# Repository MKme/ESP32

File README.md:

<p align="center">

<br>
🐦 <a href="https://twitter.com/mkmeorg">Twitter</a>
| 📺 <a href="https://www.youtube.com/mkmeorg">YouTube</a>
| 🌍 <a href="http://www.mkme.org">mkme.org</a><br>
Support this project and become a patron on <a href="http://mkme.org/patreon">Eric's Patreon</a>.<br>
Website, Forum and store are at http://mkme.org <br>
Chat with Me: <a href="https://discord.gg/j9S4Fgv">Discord</a></b>
</p>

Eric's ESP32 stuff for the various ESP32 boards and programming files in my collection.  Since the ESP32 is supported by MicroPython 
I will try to incorporate it in to more projects and videos as best I can.  

Buy an ESP32 Cam board here: https://amzn.to/2MMk2QP

Buy the ESP32 Lite Board here: https://amzn.to/2YDs3tN

Buy the OLED version here: https://amzn.to/36DUf4b

# Wemos ESP32 Lite Board

Buy the ESP 32 Lite on Amazon here: https://amzn.to/3coe2be

## Install Micropython

1.  Got to micropythong.org
2.  Download ESP32 Firmware for board
3.  Open Thonny and pick ESP32 on USB and flash firmware .bin
4.  Thonny Repl should be working  

## Wemos 32 Lite Reference Info Links

4MB Flash

Lithium battery interface, 500mA Max charging current

Default firmware: Lastest MicroPython firmware

Max serial baud rate: 256000bps

-  GPIO 22 has built in LED 

- No power LED so no wasted consumption

- https://diyprojects.io/wemos-lolin32-lite-compact-revision-lolin32-4-90/

- https://randomnerdtutorials.com/getting-started-micropython-esp32-esp8266/#:~:text=The%20code%20for%20blinking%20an%20LED%20on%20a,without%20the%20need%20to%20compile%20or%20upload%20code.

-  https://randomnerdtutorials.com/getting-started-micropython-esp32-esp8266/#:~:text=The%20code%20for%20blinking%20an%20LED%20on%20a,without%20the%20need%20to%20compile%20or%20upload%20code.

-  Not lite but same programming https://www.youtube.com/watch?v=BzAo48cFhS8&ab_channel=

# ESP 32 Cam Board

- See ResQ repo for updated ESP32 camera code but copied here for quick use

- Interesting Google Cam use https://www.youtube.com/watch?v=Upcr_rXnMQY&ab_channel=anyboards

- BME 280 I2C with ESP cam:  https://3iinc.xyz/blog/how-to-use-i2c-sensor-bme280-with-esp32cam/  

## FTDI Connections for programming: 
<br>

##  Arduino Settings for programming:

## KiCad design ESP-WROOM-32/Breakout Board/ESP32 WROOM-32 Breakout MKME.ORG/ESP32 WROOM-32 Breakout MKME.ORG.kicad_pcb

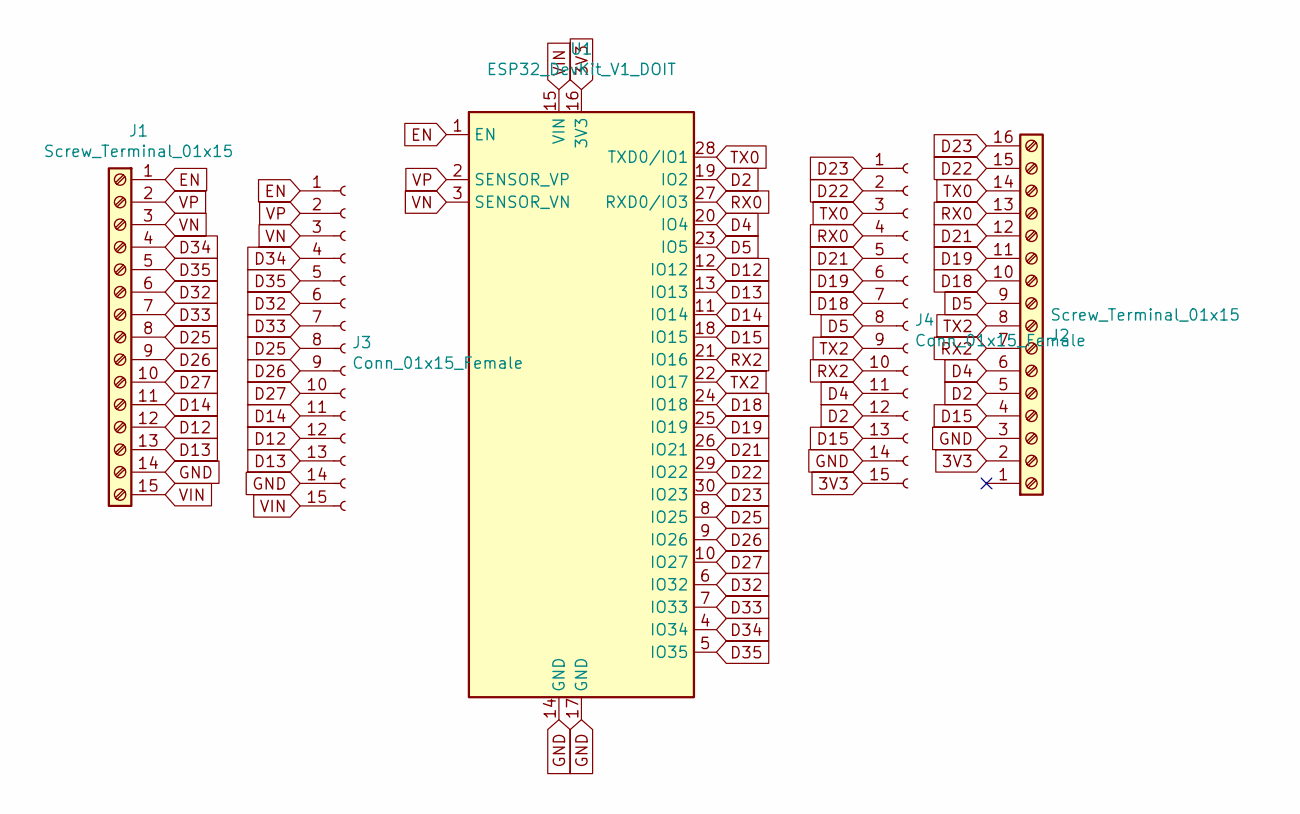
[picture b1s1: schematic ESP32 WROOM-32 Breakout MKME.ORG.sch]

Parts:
J1, J2: Screw_Terminal_01x15; TerminalBlock_Phoenix_MKDS-1,5-16-5.08_1x16_P5.08mm_Horizon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
J3, J4: Conn_01x15_Female; PinHeader_1x15_P2.54mm_Vertical
U1: ESP32_DevKit_V1_DOIT; esp32_devkit_v1_doit

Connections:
3V3: J2.2, J4.15, U1.16 (3V3)
D2: J2.5, J4.12, U1.19 (IO2)
D4: J2.6, J4.11, U1.20 (IO4)
D5: J2.9, J4.8, U1.23 (IO5)
D12: J1.12, J3.12, U1.12 (IO12)
D13: J1.13, J3.13, U1.13 (IO13)
D14: J1.11, J3.11, U1.11 (IO14)
D15: J2.4, J4.13, U1.18 (IO15)
D18: J2.10, J4.7, U1.24 (IO18)
D19: J2.11, J4.6, U1.25 (IO19)
D21: J2.12, J4.5, U1.26 (IO21)
D22: J2.15, J4.2, U1.29 (IO22)
D23: J2.16, J4.1, U1.30 (IO23)
D25: J1.8, J3.8, U1.8 (IO25)
D26: J1.9, J3.9, U1.9 (IO26)
D27: J1.10, J3.10, U1.10 (IO27)
D32: J1.6, J3.6, U1.6 (IO32)
D33: J1.7, J3.7, U1.7 (IO33)
D34: J1.4, J3.4, U1.4 (IO34)
D35: J1.5, J3.5, U1.5 (IO35)
EN: J1.1, J3.1, U1.1 (EN)
GND: J1.14, J2.3, J3.14, J4.14, U1.14 (GND), U1.17 (GND)
RX0: J2.13, J4.4, U1.27 (RXD0/IO3)
RX2: J2.7, J4.10, U1.21 (IO16)
TX0: J2.14, J4.3, U1.28 (TXD0/IO1)
TX2: J2.8, J4.9, U1.22 (IO17)
VIN: J1.15, J3.15, U1.15 (VIN)
VN: J1.3, J3.3, U1.3 (SENSOR_VN)
VP: J1.2, J3.2, U1.2 (SENSOR_VP)

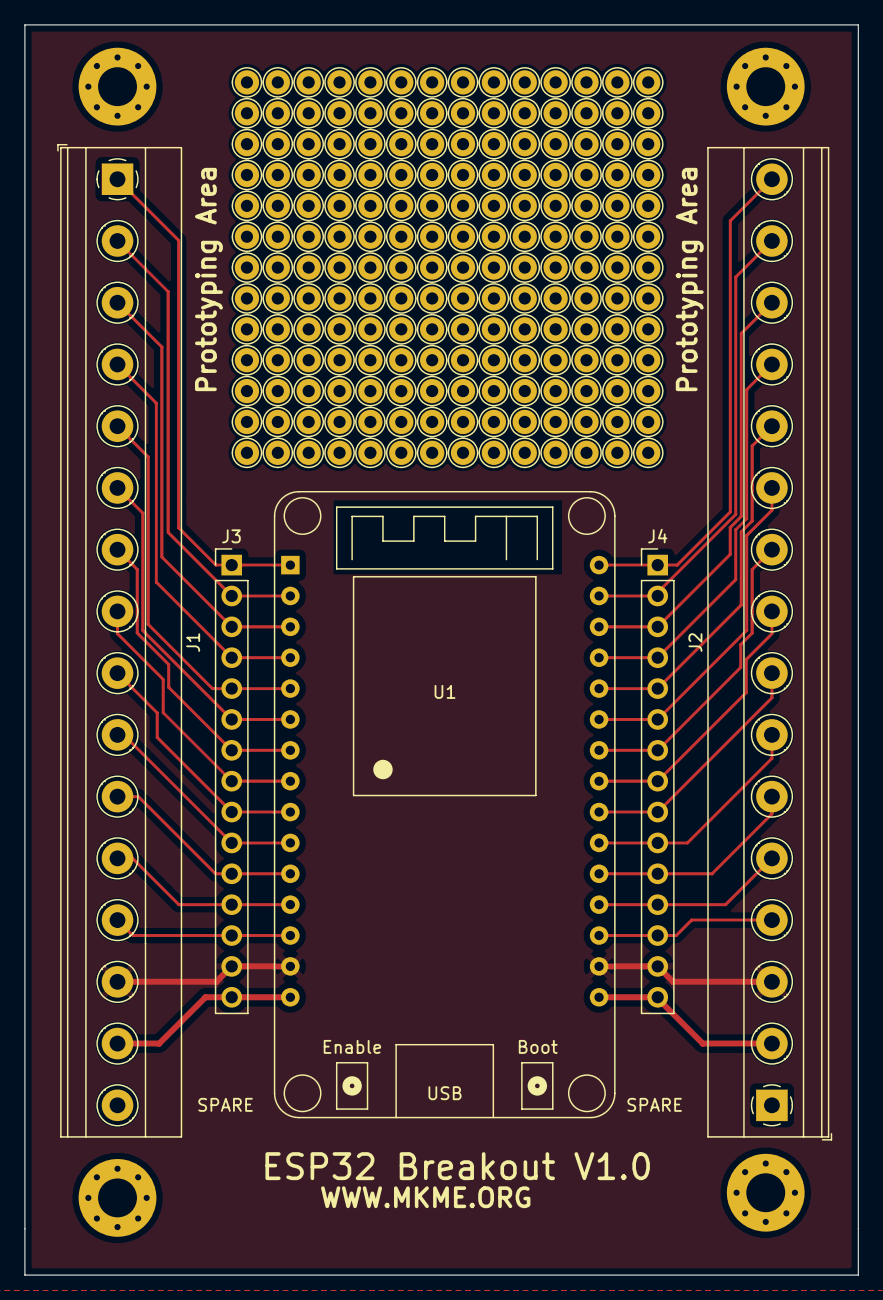
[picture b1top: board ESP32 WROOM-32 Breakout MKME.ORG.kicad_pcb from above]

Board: 2 copper layers, 68.6 x 102.9 mm, 5 parts (0 on the bottom side), 29 nets.

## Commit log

2021-02-03 ESP32 Handy dandy
2021-02-03 ESP32Cam
2021-02-06 Wemos 32 Lite Notes and info
2021-02-06 32 lite
2021-04-19 Arduino IDE updates
2021-04-23 Created KiCad Library files
    Bought from fiverr
2021-04-28 Cam stuff
2021-05-08 WROOM
2021-09-05 Breakout board Build
2021-10-10 Photos and kit updated
2021-10-16 Breakout board DONE
2021-11-25 Breakout added
2021-12-30 Final pics
2022-01-21 Added S2
2022-02-04 Fixes
